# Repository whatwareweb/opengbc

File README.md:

# opengbc
Open source reimplementation of Game Boy Color using all new components

This PCB is designed to be a complete ground-up reimplementation of the Game Boy Color. I made it because I had a knockoff GBC clone, but the overall quality was quite bad, and it could use many improvements.

This PCB is designed to fit inside a standard Game Boy Color shell.

To build this project, you'll need everything in the BOM below, as well as this PCB by leggomyfroggo. https://oshpark.com/shared_projects/jb6p7510

You'll also need a GBC power board, the Simple Gameboy Regulator is recommended. The BOM for this is included below as well. https://github.com/Jackv-makes/SGR

# BOM

|Description          |Price |Link                                                                                                                                                                                                                                                                                                                                                                                                                                                                                                                                                                                                                                                                                                                             |
|---------------------|------|---------------------------------------------------------------------------------------------------------------------------------------------------------------------------------------------------------------------------------------------------------------------------------------------------------------------------------------------------------------------------------------------------------------------------------------------------------------------------------------------------------------------------------------------------------------------------------------------------------------------------------------------------------------------------------------------------------------------------------|
|Electronic components|45.09 |N/a Mouser                                                                                                                                                                                                                                                                                                                                                                                                                                                                                                                                                                                                                                                                                                                       |
|LCD screen           |53.93 |https://www.aliexpress.us/item/3256806512370026.html?spm+AD0-a2g0o.productlist.main.4.1bc31b4b5tDKgn+ACY-algo+AF8-pvid+AD0-13bfb1cf+AC0-5558+AC0-46a5+AC0-8419+AC0-575b0f02e65b+ACY-algo+AF8-exp+AF8-id+AD0-13bfb1cf+AC0-5558+AC0-46a5+AC0-8419+AC0-575b0f02e65b+AC0-3+ACY-pdp+AF8-ext+AF8-f+AD0AJQ-7B+ACU-22order+ACU-22+ACU-3A+ACU-2233+ACU-22+ACU-2C+ACU-22eval+ACU-22+ACU-3A+ACU-221+ACU-22+ACU-7D+ACY-pdp+AF8-npi+AD0-4+ACU-40dis+ACU-21USD+ACU-2144.90+ACU-2139.40+ACU-21+ACU-21+ACU-2144.90+ACU-2139.40+ACU-21+ACU-4021030ea417540377393777504ec2d3+ACU-2112000038039232380+ACU-21sea+ACU-21US+ACU-210+ACU-21ABX+ACY-curPageLogUid+AD0-AXccxJY3e6BW+ACY-utparam+AC0-url+AD0-scene+ACU-3Asearch+ACU-7Cquery+AF8-from+ACU-3A|
|Battery terminals    |1.76  |https://www.aliexpress.us/item/3256802143018058.html?spm+AD0-a2g0o.productlist.main.2.1ca42f52f0XLYT+ACY-algo+AF8-pvid+AD0-4f75c088+AC0-b7a9+AC0-4bdc+AC0-9fec+AC0-f14cafd9035a+ACY-algo+AF8-exp+AF8-id+AD0-4f75c088+AC0-b7a9+AC0-4bdc+AC0-9fec+AC0-f14cafd9035a+AC0-1+ACY-pdp+AF8-ext+AF8-f+AD0AJQ-7B+ACU-22order+ACU-22+ACU-3A+ACU-22465+ACU-22+ACU-2C+ACU-22eval+ACU-22+ACU-3A+ACU-221+ACU-22+ACU-7D+ACY-pdp+AF8-npi+AD0-4+ACU-40dis+ACU-21USD+ACU-211.57+ACU-210.99+ACU-21+ACU-21+ACU-211.57+ACU-210.99+ACU-21+ACU-402103273e17540378404726307eab1e+ACU-2112000020111732403+ACU-21sea+ACU-21US+ACU-210+ACU-21ABX+ACY-curPageLogUid+AD0-vHGHSxM7Uol6+ACY-utparam+AC0-url+AD0-scene+ACU-3Asearch+ACU-7Cquery+AF8-from+ACU-3A   |
|Power switch         |1.23  |https://www.aliexpress.us/item/3256803358168199.html?spm+AD0-a2g0o.productlist.main.1.c6876a5fWXfoCN+ACY-algo+AF8-pvid+AD0-758d861f+AC0-75d8+AC0-4e97+AC0-a91a+AC0-33fb538aec99+ACY-algo+AF8-exp+AF8-id+AD0-758d861f+AC0-75d8+AC0-4e97+AC0-a91a+AC0-33fb538aec99+AC0-0+ACY-pdp+AF8-ext+AF8-f+AD0AJQ-7B+ACU-22order+ACU-22+ACU-3A+ACU-221273+ACU-22+ACU-2C+ACU-22eval+ACU-22+ACU-3A+ACU-221+ACU-22+ACU-7D+ACY-pdp+AF8-npi+AD0-4+ACU-40dis+ACU-21USD+ACU-211.15+ACU-210.99+ACU-21+ACU-21+ACU-211.15+ACU-210.99+ACU-21+ACU-402103247417540380137576601e1668+ACU-2112000026233474552+ACU-21sea+ACU-21US+ACU-210+ACU-21ABX+ACY-curPageLogUid+AD0-iYGJaLStAVkN+ACY-utparam+AC0-url+AD0-scene+ACU-3Asearch+ACU-7Cquery+AF8-from+ACU-3A  |
|Screws               |1.3   |https://www.aliexpress.us/item/3256806342262435.html?spm=a2g0o.productlist.main.2.6037vvgdvvgdZt&algo_pvid=6d20863a-4c9d-4d95-97a2-066ea59399f6&algo_exp_id=6d20863a-4c9d-4d95-97a2-066ea59399f6-1&pdp_ext_f=%7B%22order%22%3A%2253%22%2C%22eval%22%3A%221%22%7D&pdp_npi=6%40dis%21USD%211.30%210.99%21%21%211.30%210.99%21%402101c67a17545107211398963e3d1b%2112000037543280276%21sea%21US%210%21ABX%211%210%21&curPageLogUid=HbBrmoh2DwTp&utparam-url=scene%3Asearch%7Cquery_from%3A                                                                                                                                                                                                                                           |
|Sticker              |1.91  |https://www.aliexpress.us/item/3256808553344198.html?spm=a2g0o.productlist.main.4.6d994394kjdo2j&aem_p4p_detail=202508061308086116055938397440001812878&algo_pvid=4c040353-5d2f-4985-9663-808cbaa24eaf&algo_exp_id=4c040353-5d2f-4985-9663-808cbaa24eaf-3&pdp_ext_f=%7B%22order%22%3A%2222%22%2C%22eval%22%3A%221%22%7D&pdp_npi=6%40dis%21USD%211.91%210.99%21%21%2113.65%217.07%21%40210312d517545108882981985e3db6%2112000046472221323%21sea%21US%210%21ABX%211%210%21&curPageLogUid=yzPoZ2Nhswoy&utparam-url=scene%3Asearch%7Cquery_from%3A&search_p4p_id=202508061308086116055938397440001812878_1                                                                                                                           |
|Cartridge port       |3.83  |https://www.aliexpress.us/item/3256806628792724.html?spm=a2g0o.productlist.main.1.50395a261sjLsu&algo_pvid=1be32dde-c505-4c10-94b6-d65766154bdd&algo_exp_id=1be32dde-c505-4c10-94b6-d65766154bdd-0&pdp_ext_f=%7B%22order%22%3A%224%22%2C%22eval%22%3A%221%22%7D&pdp_npi=6%40dis%21USD%213.83%210.99%21%21%213.83%210.99%21%402103245417545116286391914ed9f4%2112000038393658608%21sea%21US%210%21ABX%211%210%21&curPageLogUid=MN4Xl2vvOewM&utparam-url=scene%3Asearch%7Cquery_from%3A                                                                                                                                                                                                                                            |
|Header pins          |3.6   |https://www.aliexpress.us/item/3256805564144874.html?spm=a2g0o.productlist.main.12.5d7e43f6f6YW6M&algo_pvid=96d58a5b-749e-49b2-9158-a494634e28b3&algo_exp_id=96d58a5b-749e-49b2-9158-a494634e28b3-13&pdp_ext_f=%7B%22order%22%3A%227%22%2C%22eval%22%3A%221%22%7D&pdp_npi=6%40dis%21USD%213.60%210.99%21%21%2125.76%217.07%21%402103244817545119088668958eb226%2112000034219097914%21sea%21US%210%21ABX%211%210%21&curPageLogUid=8kyljSDKAGiU&utparam-url=scene%3Asearch%7Cquery_from%3A                                                                                                                                                                                                                                         |
|PCBs                 |11.3  |n/a jlc                                                                                                                                                                                                                                                                                                                                                                                                                                                                                                                                                                                                                                                                                                                          |
|Stencils             |20.72 |n/a jlc                                                                                                                                                                                                                                                                                                                                                                                                                                                                                                                                                                                                                                                                                                                          |
|pcb shipping         |11.4  |n/a jlc                                                                                                                                                                                                                                                                                                                                                                                                                                                                                                                                                                                                                                                                                                                          |
|total cost:          |156.07|                                                                                                                                                                                                                                                                                                                                                                                                                                                                                                                                                                                                                                                                                                                                 |

[Creative Commons Attribution-ShareAlike 4.0 International (CC BY-SA 4.0) license](https://creativecommons.org/licenses/by-sa/4.0/)

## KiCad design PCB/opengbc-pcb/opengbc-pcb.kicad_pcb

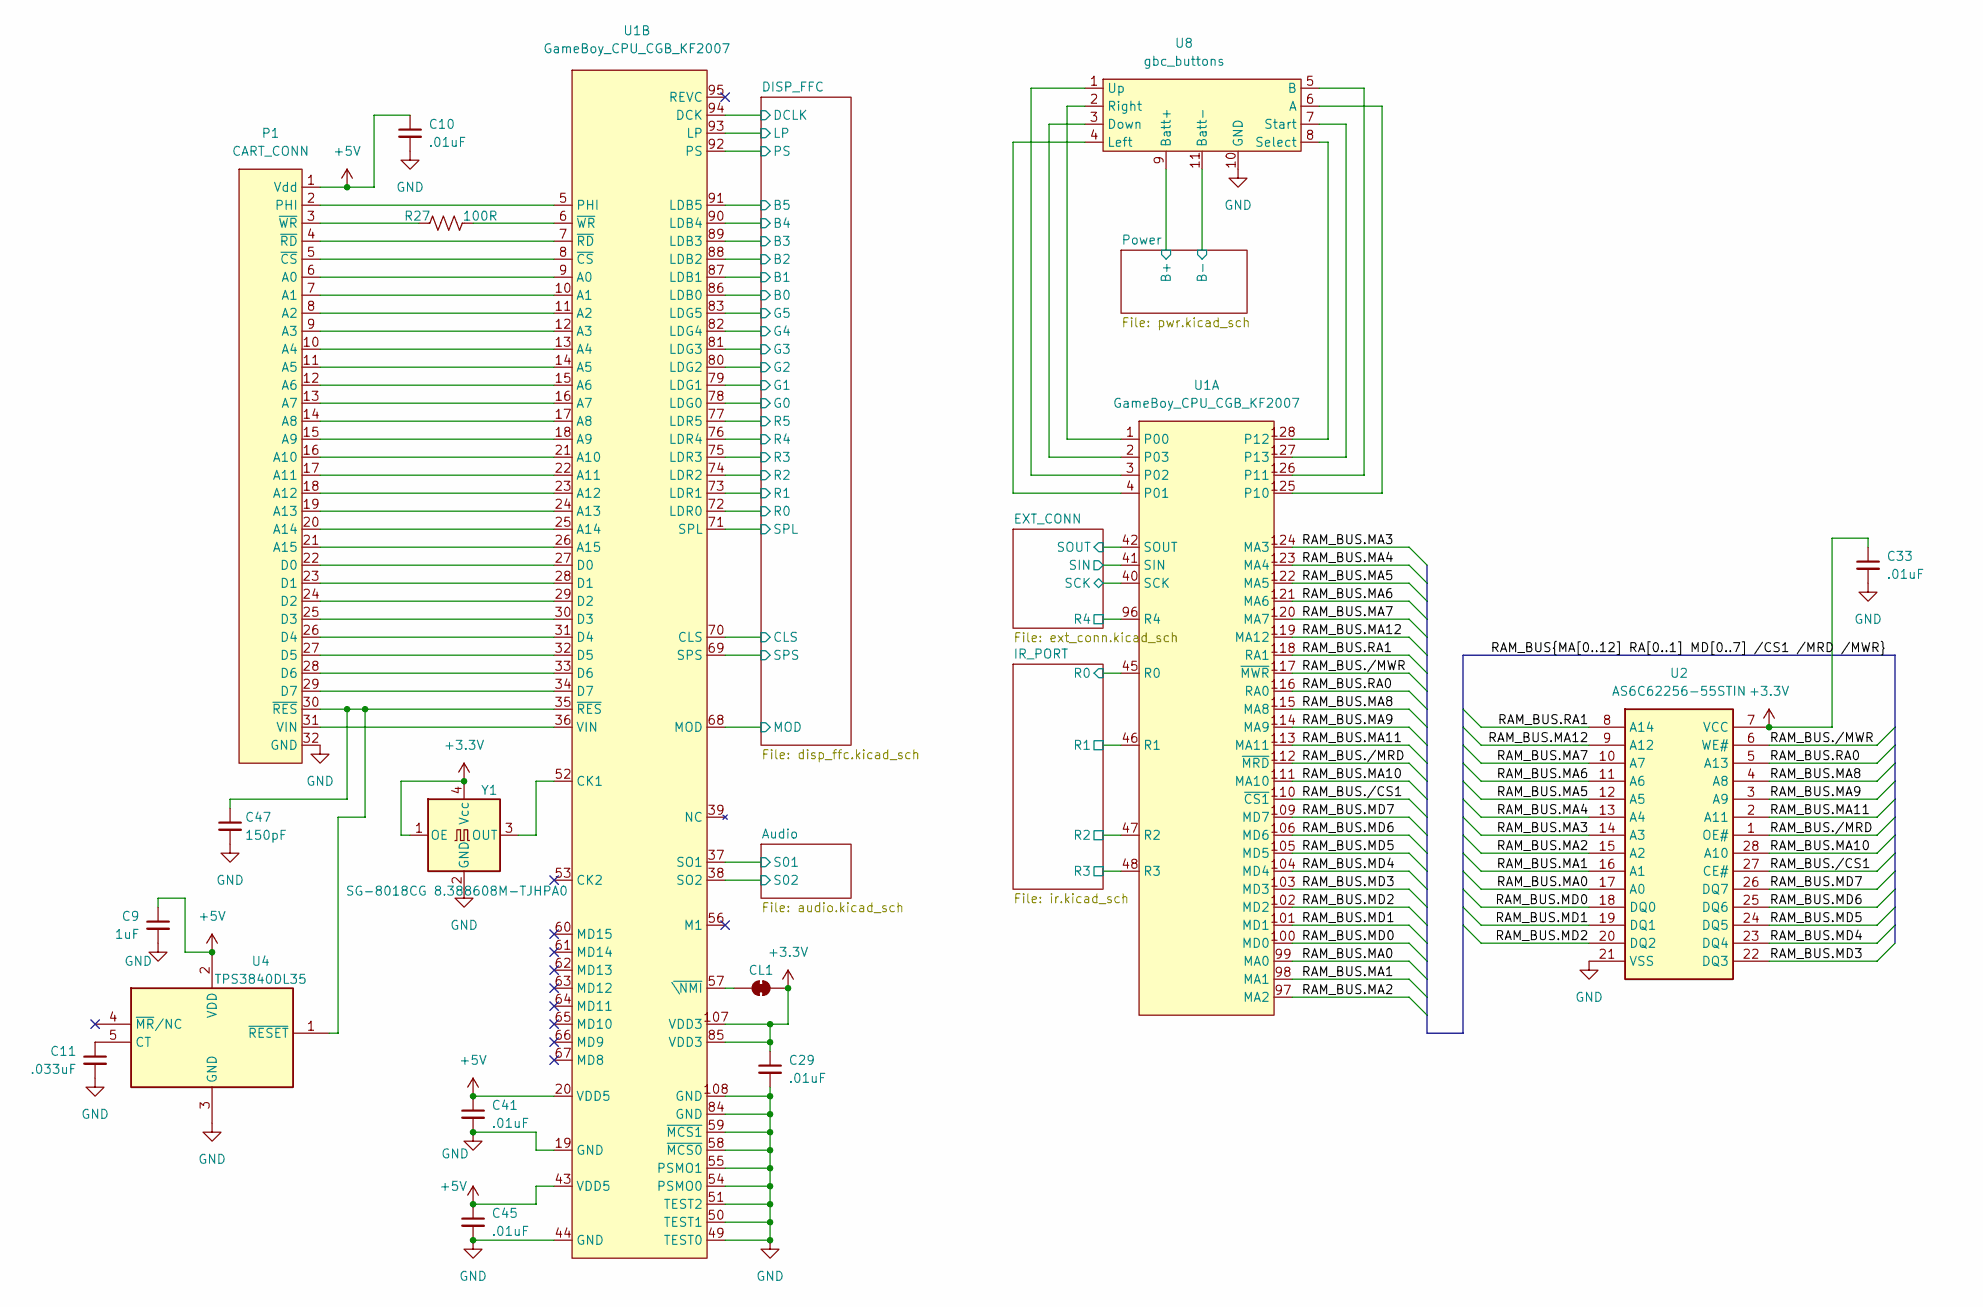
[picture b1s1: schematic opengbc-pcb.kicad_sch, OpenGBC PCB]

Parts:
C9: 1uF; C_0603_1608Metric_Pad1.08x0.95mm_HandSolder; Mouser Part Number 963-JMK107BJ105MA-T
C10, C29, C33, C41, C45: .01uF; C_0603_1608Metric_Pad1.08x0.95mm_HandSolder; Mouser Part Number 81-GRT188R72A103KE1D
C11: .033uF; C_0603_1608Metric_Pad1.08x0.95mm_HandSolder; Mouser Part Number 603-CC603JRX7R8BB333
C47: 150pF; C_0603_1608Metric_Pad1.08x0.95mm_HandSolder; Mouser Part Number 187-CL10C151JB81PNC
CL1: SolderJumper_2_Bridged; SolderJumper-2_P1.3mm_Bridged_RoundedPad1.0x1.5mm
P1: CART_CONN; gbc_mgb_cart_slot
R27: 100R; R_0603_1608Metric_Pad0.98x0.95mm_HandSolder; Mouser Part Number 791-RMC1/16-101JTP10
U1: GameBoy_CPU_CGB_KF2007; LQFP-128_14x20mm_P0.5mm
U2: AS6C62256-55STIN; TSOP-I-28_11.8x8mm_P0.55mm; Mouser Part Number 913-AS6C62256-55STIN
U4: TPS3840DL35; SOT-23-5_HandSoldering; Mouser Part Number 595-TPS3840DL35DBVR
U8: gbc_buttons
Y1: SG-8018CG 8.388608M-TJHPA0; Oscillator_SMD_SeikoEpson_SG8002CE-4Pin_3.2x2.5mm; Mouser Part Number 732-CE838868MTJHPA

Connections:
+3.3V: C29.1, C33.1, CL1.2 (B), U1.85 (VDD3), U1.107 (VDD3), U2.7 (VCC), Y1.1 (OE), Y1.4 (Vcc); also elsewhere on the board
+5V: C9.1, C10.1, C41.1, C45.1, P1.1 (Vdd), U1.20 (VDD5), U1.43 (VDD5), U4.2 (VDD); also elsewhere on the board
/Audio/S01: U1.37 (SO1); also elsewhere on the board
/Audio/S02: U1.38 (SO2); also elsewhere on the board
/DISP_FFC/B0: U1.86 (LDB0); also elsewhere on the board
/DISP_FFC/B1: U1.87 (LDB1); also elsewhere on the board
/DISP_FFC/B2: U1.88 (LDB2); also elsewhere on the board
/DISP_FFC/B3: U1.89 (LDB3); also elsewhere on the board
/DISP_FFC/B4: U1.90 (LDB4); also elsewhere on the board
/DISP_FFC/B5: U1.91 (LDB5); also elsewhere on the board
/DISP_FFC/CLS: U1.70 (CLS); also elsewhere on the board
/DISP_FFC/DCLK: U1.94 (DCK); also elsewhere on the board
/DISP_FFC/G0: U1.78 (LDG0); also elsewhere on the board
/DISP_FFC/G1: U1.79 (LDG1); also elsewhere on the board
/DISP_FFC/G2: U1.80 (LDG2); also elsewhere on the board
/DISP_FFC/G3: U1.81 (LDG3); also elsewhere on the board
/DISP_FFC/G4: U1.82 (LDG4); also elsewhere on the board
/DISP_FFC/G5: U1.83 (LDG5); also elsewhere on the board
/DISP_FFC/LP: U1.93 (LP); also elsewhere on the board
/DISP_FFC/MOD: U1.68 (MOD); also elsewhere on the board
/DISP_FFC/PS: U1.92 (PS); also elsewhere on the board
/DISP_FFC/R0: U1.72 (LDR0); also elsewhere on the board
/DISP_FFC/R1: U1.73 (LDR1); also elsewhere on the board
/DISP_FFC/R2: U1.74 (LDR2); also elsewhere on the board
/DISP_FFC/R3: U1.75 (LDR3); also elsewhere on the board
/DISP_FFC/R4: U1.76 (LDR4); also elsewhere on the board
/DISP_FFC/R5: U1.77 (LDR5); also elsewhere on the board
/DISP_FFC/SPL: U1.71 (SPL); also elsewhere on the board
/DISP_FFC/SPS: U1.69 (SPS); also elsewhere on the board
/EXT_CONN/R4: U1.96 (R4); also elsewhere on the board
/EXT_CONN/SCK: U1.40 (SCK); also elsewhere on the board
/EXT_CONN/SIN: U1.41 (SIN); also elsewhere on the board
/EXT_CONN/SOUT: U1.42 (SOUT); also elsewhere on the board
/IR_PORT/R0: U1.45 (R0); also elsewhere on the board
/IR_PORT/R1: U1.46 (R1); also elsewhere on the board
/IR_PORT/R2: U1.47 (R2); also elsewhere on the board
/IR_PORT/R3: U1.48 (R3); also elsewhere on the board
/Power/B+: U8.9 (Batt+); also elsewhere on the board
/Power/B-: U8.11 (Batt-); also elsewhere on the board
/RAM_BUS.MA0: U1.99 (MA0), U2.17 (A0)
/RAM_BUS.MA1: U1.98 (MA1), U2.16 (A1)
/RAM_BUS.MA2: U1.97 (MA2), U2.15 (A2)
/RAM_BUS.MA3: U1.124 (MA3), U2.14 (A3)
/RAM_BUS.MA4: U1.123 (MA4), U2.13 (A4)
/RAM_BUS.MA5: U1.122 (MA5), U2.12 (A5)
/RAM_BUS.MA6: U1.121 (MA6), U2.11 (A6)
/RAM_BUS.MA7: U1.120 (MA7), U2.10 (A7)
/RAM_BUS.MA8: U1.115 (MA8), U2.4 (A8)
/RAM_BUS.MA9: U1.114 (MA9), U2.3 (A9)
/RAM_BUS.MA10: U1.111 (MA10), U2.28 (A10)
/RAM_BUS.MA11: U1.113 (MA11), U2.2 (A11)
/RAM_BUS.MA12: U1.119 (MA12), U2.9 (A12)
/RAM_BUS.MD0: U1.100 (MD0), U2.18 (DQ0)
/RAM_BUS.MD1: U1.101 (MD1), U2.19 (DQ1)
/RAM_BUS.MD2: U1.102 (MD2), U2.20 (DQ2)
/RAM_BUS.MD3: U1.103 (MD3), U2.22 (DQ3)
/RAM_BUS.MD4: U1.104 (MD4), U2.23 (DQ4)
/RAM_BUS.MD5: U1.105 (MD5), U2.24 (DQ5)
/RAM_BUS.MD6: U1.106 (MD6), U2.25 (DQ6)
/RAM_BUS.MD7: U1.109 (MD7), U2.26 (DQ7)
/RAM_BUS.RA0: U1.116 (RA0), U2.5 (A13)
/RAM_BUS.RA1: U1.118 (RA1), U2.8 (A14)
/RAM_BUS./CS1: U1.110 (~CS1), U2.27 (CE#)
/RAM_BUS./MRD: U1.112 (~MRD), U2.1 (OE#)
/RAM_BUS./MWR: U1.117 (~MWR), U2.6 (WE#)
GND: C9.2, C10.2, C11.2, C29.2, C33.2, C41.2, C45.2, C47.2, P1.32 (GND), U1.19 (GND), U1.44 (GND), U1.49 (TEST0), U1.50 (TEST1), U1.51 (TEST2), U1.54 (PSMO0), U1.55 (PSMO1), U1.58 (~MCS0), U1.59 (~MCS1), U1.84 (GND), U1.108 (GND), U2.21 (VSS), U4.3 (GND), U8.10 (GND), Y1.2 (GND); also elsewhere on the board
unnamed: CL1.1 (A), U1.57 (~\NMI)
unnamed: P1.6 (A0), U1.9 (A0)
unnamed: P1.7 (A1), U1.10 (A1)
unnamed: P1.8 (A2), U1.11 (A2)
unnamed: P1.9 (A3), U1.12 (A3)
unnamed: P1.10 (A4), U1.13 (A4)
unnamed: P1.11 (A5), U1.14 (A5)
unnamed: P1.12 (A6), U1.15 (A6)
unnamed: P1.13 (A7), U1.16 (A7)
unnamed: P1.14 (A8), U1.17 (A8)
unnamed: P1.15 (A9), U1.18 (A9)
unnamed: P1.16 (A10), U1.21 (A10)
unnamed: P1.17 (A11), U1.22 (A11)
unnamed: P1.18 (A12), U1.23 (A12)
unnamed: P1.19 (A13), U1.24 (A13)
unnamed: P1.20 (A14), U1.25 (A14)
unnamed: P1.21 (A15), U1.26 (A15)
unnamed: P1.22 (D0), U1.27 (D0)
unnamed: P1.23 (D1), U1.28 (D1)
unnamed: P1.24 (D2), U1.29 (D2)
unnamed: P1.25 (D3), U1.30 (D3)
unnamed: P1.26 (D4), U1.31 (D4)
unnamed: P1.27 (D5), U1.32 (D5)
unnamed: P1.28 (D6), U1.33 (D6)
unnamed: P1.29 (D7), U1.34 (D7)
unnamed: P1.2 (PHI), U1.5 (PHI)
unnamed: P1.31 (VIN), U1.36 (VIN)
unnamed: P1.5 (~CS), U1.8 (~CS)
unnamed: P1.4 (~RD), U1.7 (~RD)
unnamed: C47.1, P1.30 (~RES), U1.35 (~RES), U4.1 (~RESET)
unnamed: P1.3 (~WR), R27.1
unnamed: U1.1 (P00), U8.2 (Right)
unnamed: U1.4 (P01), U8.4 (Left)
unnamed: U1.3 (P02), U8.1 (Up)
unnamed: U1.2 (P03), U8.3 (Down)
unnamed: U1.125 (P10), U8.6 (A)
unnamed: U1.126 (P11), U8.5 (B)
unnamed: U1.128 (P12), U8.8 (Select)
unnamed: U1.127 (P13), U8.7 (Start)
unnamed: U1.52 (CK1), Y1.3 (OUT)
unnamed: R27.2, U1.6 (~WR)
unnamed: C11.1, U4.5 (CT)

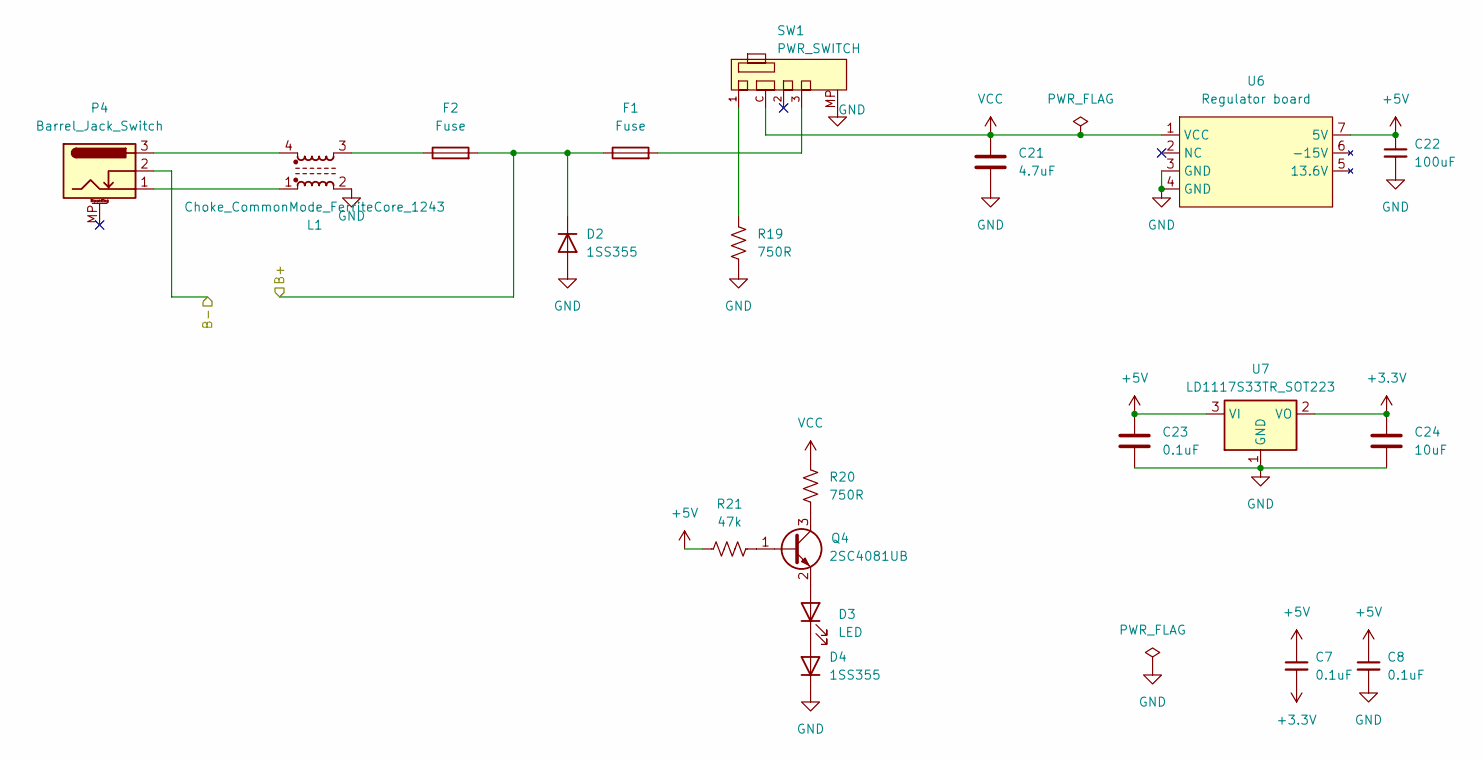
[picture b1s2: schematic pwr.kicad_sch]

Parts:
C7, C8, C23: 0.1uF; C_0603_1608Metric_Pad1.08x0.95mm_HandSolder; Mouser Part Number 81-GRM033R61C104KE4D
C21: 4.7uF; C_0603_1608Metric_Pad1.08x0.95mm_HandSolder; Mouser Part Number 187-CL10A475KP8NNNC
C22: 100uF; CP_Elec_5x5.3; Mouser Part Number 710-865080142007
C24: 10uF; C_0603_1608Metric_Pad1.08x0.95mm_HandSolder; Mouser Part Number 187-CL10A106KP8NNNC
D2, D4: 1SS355; D_SOD-323_HandSoldering; Mouser Part Number 755-1SS355VMTE-17
D3: LED; LED_D3.0mm; Mouser Part Number 710-151033RS03000
F1, F2: Fuse; Fuse_0603_1608Metric_Pad1.05x0.95mm_HandSolder; Mouser Part Number 594-MFU0603FF01000P1
L1: Choke_CommonMode_FerriteCore_1243; L_CommonModeChoke_Coilcraft_1812CAN; Mouser Part Number 710-744235601
P4: Barrel_Jack_Switch; SWITCHCRAFT_RAPC752SX; Mouser Part Number 502-RAPC752SX
Q4: 2SC4081UB; SOT-323_SC-70; Mouser Part Number 755-2SC4081UBTLR
R19, R20: 750R; R_0603_1608Metric_Pad0.98x0.95mm_HandSolder; Mouser Part Number 708-RMCF0603FT750R
R21: 47k; R_0603_1608Metric_Pad0.98x0.95mm_HandSolder; Mouser Part Number 603-RC0603JR-1047KL
SW1: PWR_SWITCH; gbc_PowerSwitch
U6: Regulator board; GBC-PWRBD
U7: LD1117S33TR_SOT223; SOT-223-3_TabPin2; Mouser Part Number 511-LD1117S33

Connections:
+3.3V: C7.2, C24.1, U7.2 (VO); also elsewhere on the board
+5V: C7.1, C8.1, C22.1, C23.1, R21.1, U6.7 (5V), U7.3 (VI); also elsewhere on the board
/Power/B+: D2.1 (K), F1.1, F2.2; also elsewhere on the board
/Power/B-: P4.2; also elsewhere on the board
GND: C8.2, C21.2, C22.2, C23.2, C24.2, D2.2 (A), D4.1 (K), L1.2, R19.2, SW1.MP, U6.3 (GND), U6.4 (GND), U7.1 (GND); also elsewhere on the board
unnamed: D3.2 (A), Q4.2 (E)
unnamed: D3.1 (K), D4.2 (A)
unnamed: F1.2, SW1.3
unnamed: F2.1, L1.3
unnamed: L1.1, P4.1
unnamed: L1.4, P4.3
unnamed: Q4.1 (B), R21.2
unnamed: Q4.3 (C), R20.2
unnamed: R19.1, SW1.1
VCC: C21.1, R20.1, SW1.C, U6.1 (VCC)

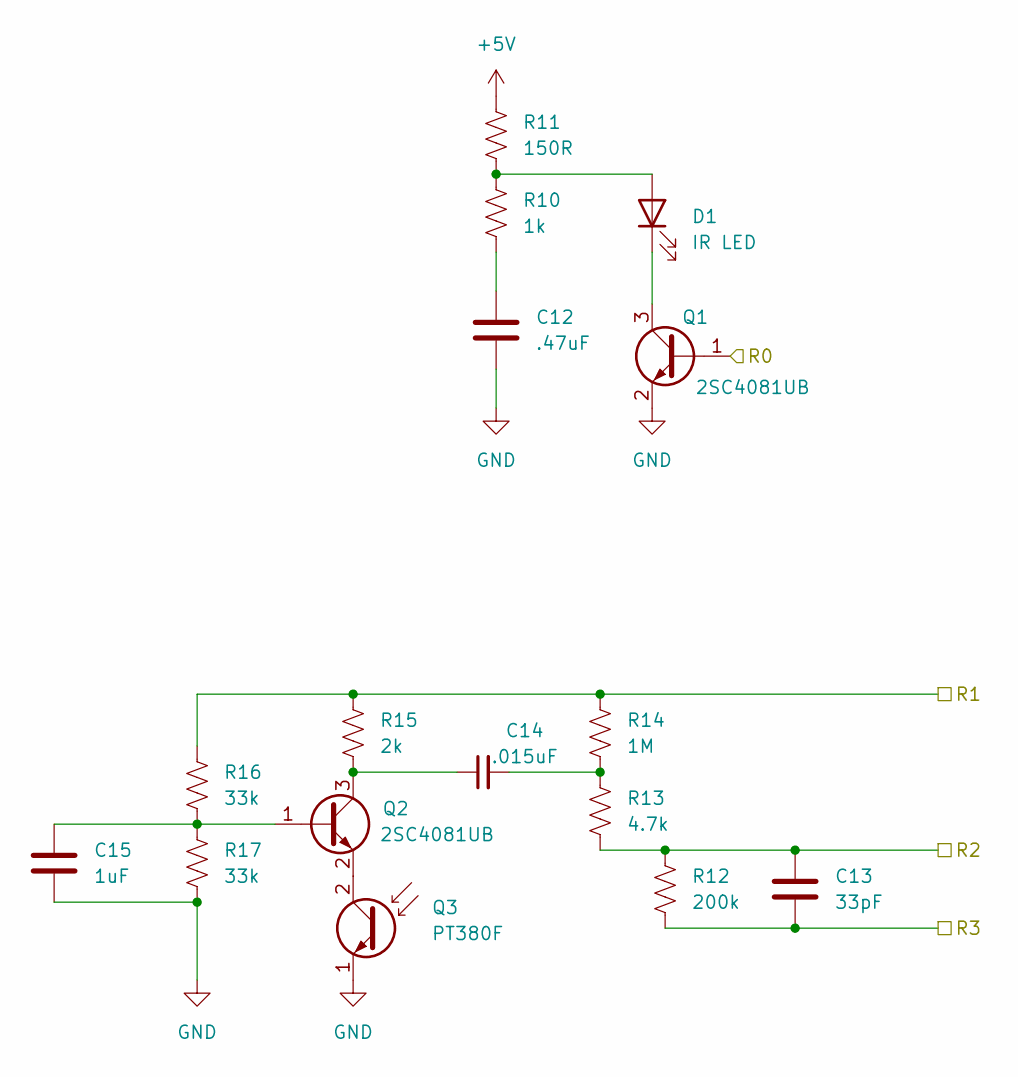
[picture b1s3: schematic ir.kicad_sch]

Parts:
C12: .47uF; C_0603_1608Metric_Pad1.08x0.95mm_HandSolder; Mouser Part Number 810-CGA3E2X5R1A474MA
C13: 33pF; C_0603_1608Metric_Pad1.08x0.95mm_HandSolder; Mouser Part Number 187-CL10C330JB8NNND
C14: .015uF; C_0603_1608Metric_Pad1.08x0.95mm_HandSolder; Mouser Part Number 80-C0603C153K4RECTU
C15: 1uF; C_0603_1608Metric_Pad1.08x0.95mm_HandSolder; Mouser Part Number 963-JMK107BJ105MA-T
D1: IR LED; gbc_ir_leds
Q1, Q2: 2SC4081UB; SOT-323_SC-70; Mouser Part Number 755-2SC4081UBTLR
Q3: PT380F; gbc_ir_leds
R10: 1k; R_0603_1608Metric_Pad0.98x0.95mm_HandSolder; Mouser Part Number 603-AC0603JR-131KL
R11: 150R; R_0603_1608Metric_Pad0.98x0.95mm_HandSolder; Mouser Part Number 708-RMCF0603JT150R
R12: 200k; R_0603_1608Metric_Pad0.98x0.95mm_HandSolder; Mouser Part Number 603-AC0603JR-07200KL
R13: 4.7k; R_0603_1608Metric_Pad0.98x0.95mm_HandSolder; Mouser Part Number 791-RMC16-472JTP
R14: 1M; R_0603_1608Metric_Pad0.98x0.95mm_HandSolder; Mouser Part Number 279-CRG0603F1M0
R15: 2k; R_0603_1608Metric_Pad0.98x0.95mm_HandSolder; Mouser Part Number 603-RT0603DRE072KL
R16, R17: 33k; R_0603_1608Metric_Pad0.98x0.95mm_HandSolder; Mouser Part Number 791-WR06X333JTL

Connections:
+5V: R11.1; also elsewhere on the board
/IR_PORT/R0: Q1.1 (B); also elsewhere on the board
/IR_PORT/R1: R14.1, R15.1, R16.1; also elsewhere on the board
/IR_PORT/R2: C13.1, R12.1, R13.2; also elsewhere on the board
/IR_PORT/R3: C13.2, R12.2; also elsewhere on the board
GND: C12.2, C15.2, Q1.2 (E), Q3.1 (E), R17.2; also elsewhere on the board
unnamed: C12.1, R10.2
unnamed: C14.2, R13.1, R14.2
unnamed: D1.2 (A), R10.1, R11.2
unnamed: D1.1 (K), Q1.3 (C)
unnamed: C15.1, Q2.1 (B), R16.2, R17.1
unnamed: C14.1, Q2.3 (C), R15.2
unnamed: Q2.2 (E), Q3.2 (C)

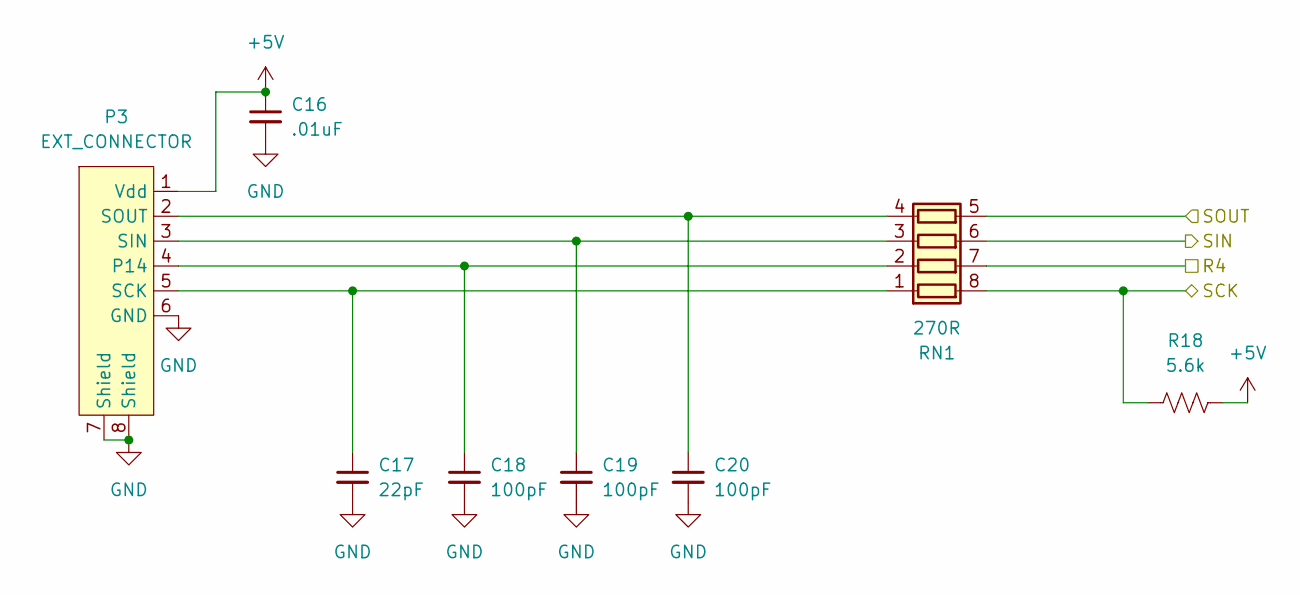
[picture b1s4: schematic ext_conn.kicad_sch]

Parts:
C16: .01uF; C_0603_1608Metric_Pad1.08x0.95mm_HandSolder; Mouser Part Number 81-GRT188R72A103KE1D
C17: 22pF; C_0603_1608Metric_Pad1.08x0.95mm_HandSolder; Mouser Part Number 810-C1608C0G1H220J
C18, C19, C20: 100pF; C_0603_1608Metric_Pad1.08x0.95mm_HandSolder; Mouser Part Number 77-VJ0603Y101MXACBC
P3: EXT_CONNECTOR; gbc-link-cable-adapter
R18: 5.6k; R_0603_1608Metric_Pad0.98x0.95mm_HandSolder; Mouser Part Number 71-CRCW06035K60FKEAC
RN1: 270R; R_Array_Concave_4x0603; Mouser Part Number 603-AC0603FR-07270RL

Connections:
+5V: C16.1, P3.1 (Vdd), R18.2; also elsewhere on the board
/EXT_CONN/R4: RN1.7 (R2.2); also elsewhere on the board
/EXT_CONN/SCK: R18.1, RN1.8 (R1.2); also elsewhere on the board
/EXT_CONN/SIN: RN1.6 (R3.2); also elsewhere on the board
/EXT_CONN/SOUT: RN1.5 (R4.2); also elsewhere on the board
GND: C16.2, C17.2, C18.2, C19.2, C20.2, P3.6 (GND), P3.7 (Shield), P3.8 (Shield); also elsewhere on the board
unnamed: C18.1, P3.4 (P14), RN1.2 (R2.1)
unnamed: C17.1, P3.5 (SCK), RN1.1 (R1.1)
unnamed: C19.1, P3.3 (SIN), RN1.3 (R3.1)
unnamed: C20.1, P3.2 (SOUT), RN1.4 (R4.1)

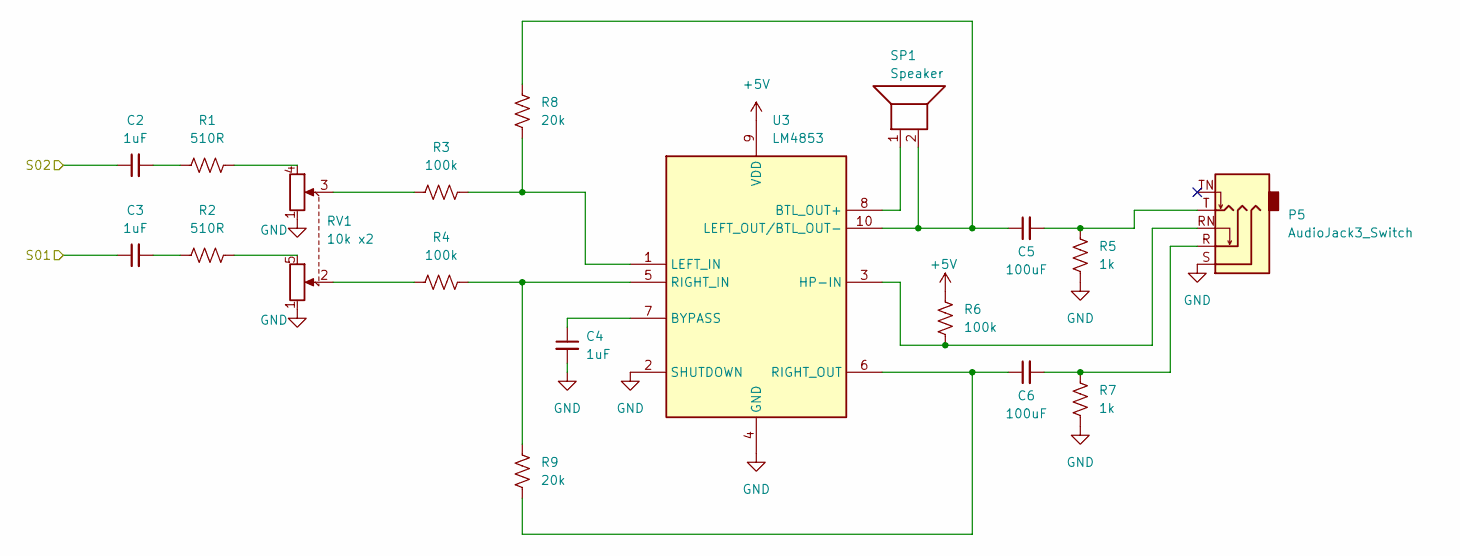
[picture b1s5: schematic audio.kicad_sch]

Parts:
C2, C3, C4: 1uF; C_0603_1608Metric_Pad1.08x0.95mm_HandSolder; Mouser Part Number 963-JMK107BJ105MA-T
C5, C6: 100uF; C_1206_3216Metric_Pad1.33x1.80mm_HandSolder; Mouser Part Number 187-CL31A107MQHNNWE
P5: AudioJack3_Switch; audio_jack; Mouser Part Number 490-SJ1-3525N
R1, R2: 510R; R_0603_1608Metric_Pad0.98x0.95mm_HandSolder; Mouser Part Number 791-WR06X511JTL
R3, R4, R6: 100k; R_0603_1608Metric_Pad0.98x0.95mm_HandSolder; Mouser Part Number 279-CRGCQ0603F100K
R5, R7: 1k; R_0603_1608Metric_Pad0.98x0.95mm_HandSolder; Mouser Part Number 603-AC0603JR-131KL
R8, R9: 20k; R_0603_1608Metric_Pad0.98x0.95mm_HandSolder; Mouser Part Number 660-RN73R1JTD2002F25
RV1: 10k x2; gbc_volume_wheel; Mouser Part Number 688-RK10J12R0A0B
SP1: Speaker; PinHeader_1x02_P1.00mm_Vertical
U3: LM4853; VSSOP-10_3x3mm_P0.5mm; Mouser Part Number 926-LM4853MM/NOPB

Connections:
+5V: R6.1, U3.9 (VDD); also elsewhere on the board
/Audio/S01: C3.1; also elsewhere on the board
/Audio/S02: C2.1; also elsewhere on the board
GND: C4.2, P5.S, R5.2, R7.2, RV1.1 (GND), U3.2 (SHUTDOWN), U3.4 (GND); also elsewhere on the board
unnamed: C2.2, R1.1
unnamed: C3.2, R2.1
unnamed: C5.2, P5.T, R5.1
unnamed: C6.2, P5.R, R7.1
unnamed: R3.1, RV1.3 (S02_OUT)
unnamed: R4.1, RV1.2 (S02_OUT)
unnamed: R2.2, RV1.5 (S01_IN)
unnamed: R1.2, RV1.4 (S02_IN)
unnamed: SP1.1, U3.8 (BTL_OUT+)
unnamed: C4.1, U3.7 (BYPASS)
unnamed: P5.RN, R6.2, U3.3 (HP-IN)
unnamed: R3.2, R8.1, U3.1 (LEFT_IN)
unnamed: C5.1, R8.2, SP1.2, U3.10 (LEFT_OUT/BTL_OUT-)
unnamed: R4.2, R9.2, U3.5 (RIGHT_IN)
unnamed: C6.1, R9.1, U3.6 (RIGHT_OUT)

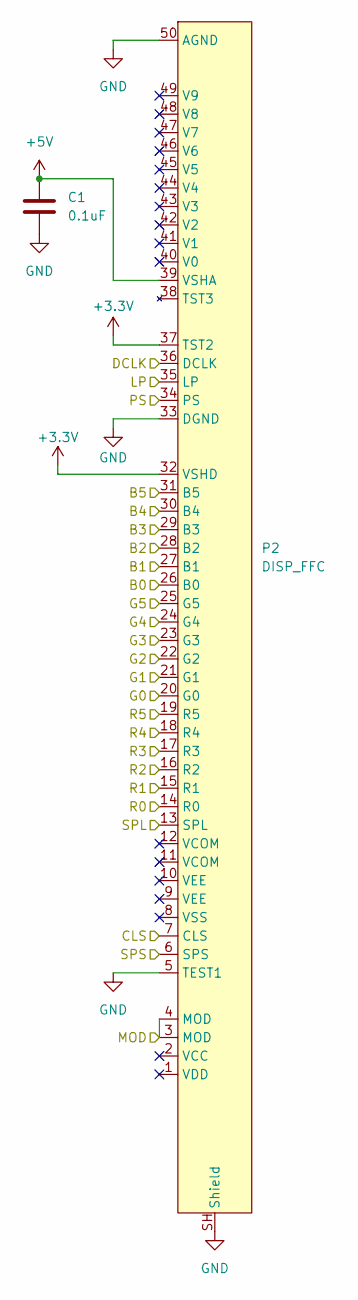
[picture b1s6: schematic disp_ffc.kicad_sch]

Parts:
C1: 0.1uF; C_0603_1608Metric_Pad1.08x0.95mm_HandSolder; Mouser Part Number 81-GRM033R61C104KE4D
P2: DISP_FFC; AMPHENOL_62684-502100AHLF; Mouser Part Number 649-62684-502100AHLF

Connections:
+3.3V: P2.32 (VSHD), P2.37 (TST2); also elsewhere on the board
+5V: C1.1, P2.39 (VSHA); also elsewhere on the board
/DISP_FFC/B0: P2.26 (B0); also elsewhere on the board
/DISP_FFC/B1: P2.27 (B1); also elsewhere on the board
/DISP_FFC/B2: P2.28 (B2); also elsewhere on the board
/DISP_FFC/B3: P2.29 (B3); also elsewhere on the board
/DISP_FFC/B4: P2.30 (B4); also elsewhere on the board
/DISP_FFC/B5: P2.31 (B5); also elsewhere on the board
/DISP_FFC/CLS: P2.7 (CLS); also elsewhere on the board
/DISP_FFC/DCLK: P2.36 (DCLK); also elsewhere on the board
/DISP_FFC/G0: P2.20 (G0); also elsewhere on the board
/DISP_FFC/G1: P2.21 (G1); also elsewhere on the board
/DISP_FFC/G2: P2.22 (G2); also elsewhere on the board
/DISP_FFC/G3: P2.23 (G3); also elsewhere on the board
/DISP_FFC/G4: P2.24 (G4); also elsewhere on the board
/DISP_FFC/G5: P2.25 (G5); also elsewhere on the board
/DISP_FFC/LP: P2.35 (LP); also elsewhere on the board
/DISP_FFC/MOD: P2.3 (MOD), P2.4 (MOD); also elsewhere on the board
/DISP_FFC/PS: P2.34 (PS); also elsewhere on the board
/DISP_FFC/R0: P2.14 (R0); also elsewhere on the board
/DISP_FFC/R1: P2.15 (R1); also elsewhere on the board
/DISP_FFC/R2: P2.16 (R2); also elsewhere on the board
/DISP_FFC/R3: P2.17 (R3); also elsewhere on the board
/DISP_FFC/R4: P2.18 (R4); also elsewhere on the board
/DISP_FFC/R5: P2.19 (R5); also elsewhere on the board
/DISP_FFC/SPL: P2.13 (SPL); also elsewhere on the board
/DISP_FFC/SPS: P2.6 (SPS); also elsewhere on the board
GND: C1.2, P2.5 (TEST1), P2.33 (DGND), P2.50 (AGND), P2.SH (Shield); also elsewhere on the board

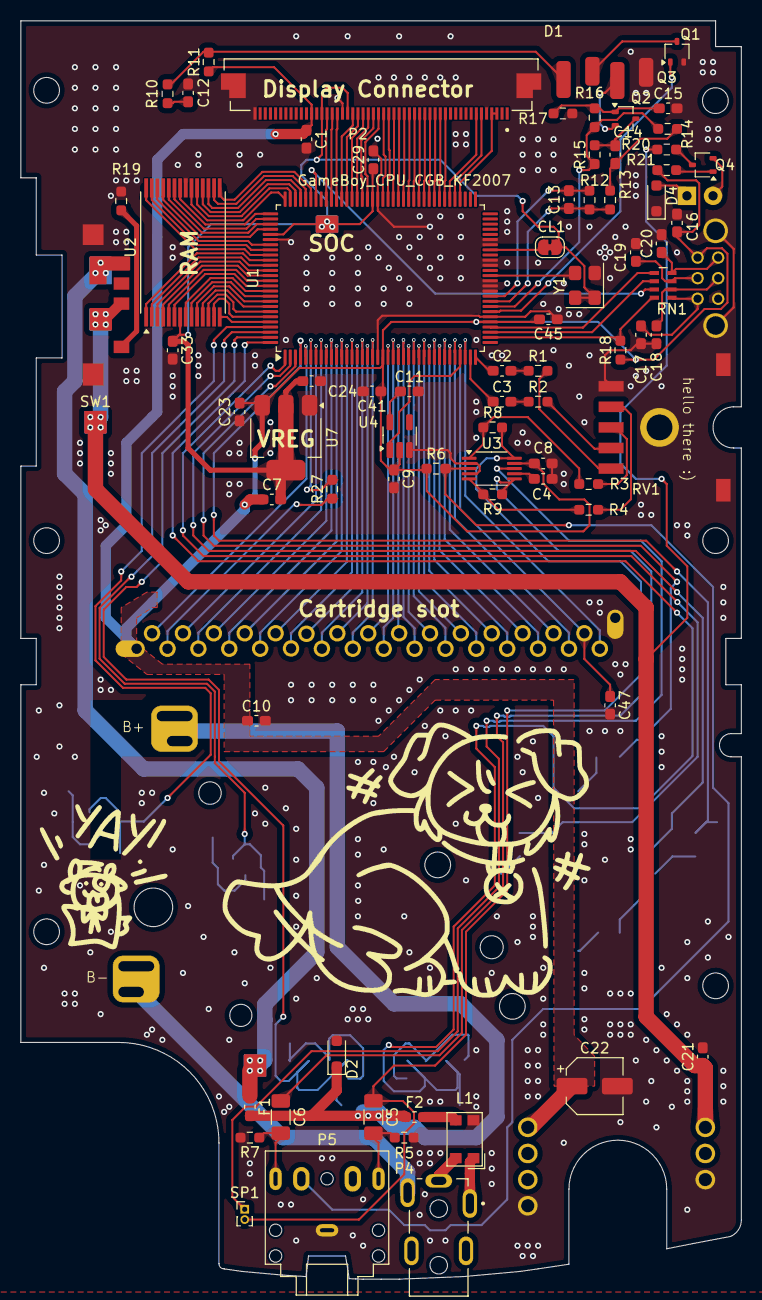
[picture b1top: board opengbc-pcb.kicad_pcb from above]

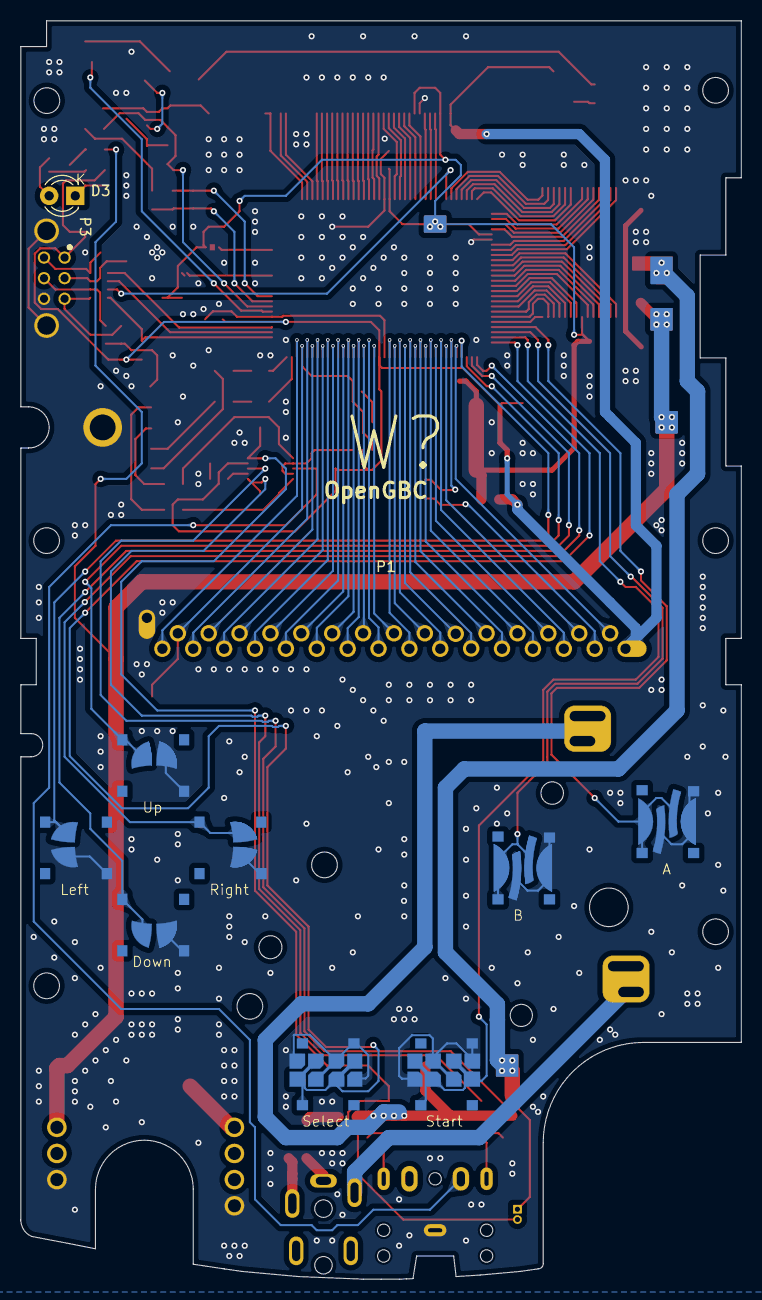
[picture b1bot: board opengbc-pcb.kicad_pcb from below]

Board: 2 copper layers, 70.0 x 122.2 mm, 80 parts (5 on the bottom side), 144 nets.

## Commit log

2025-07-16 add pcb
2025-07-16 add journal
2025-07-20 rework dir structure
2025-07-20 remove extra dir
2025-07-23 update schematics and journal and add library files
2025-07-27 update audio schematic
2025-07-28 whole bunch of schematic updates
2025-08-01 :eyes:
2025-08-01 fix journal
2025-08-01 update bom
2025-08-01 add bom csv
2025-08-04 update schematic
2025-08-06 I HATE KICAD
2025-08-06 schematic or smth idk
2025-08-06 footprints
2025-08-06 finish the thing
2025-08-06 schematic stuff
2025-08-06 fix bom
2025-08-06 update readme price
2025-08-12 GROUND VIAS RAAAHHHHH also artwork n stuff
2025-08-12 make it more fun looking
2025-08-14 pcb minor updates
2025-09-03 update ground vias mostly and other pcb shenanigans
2025-09-03 update readme and fill zones/drc
2025-11-10 remove step cad
